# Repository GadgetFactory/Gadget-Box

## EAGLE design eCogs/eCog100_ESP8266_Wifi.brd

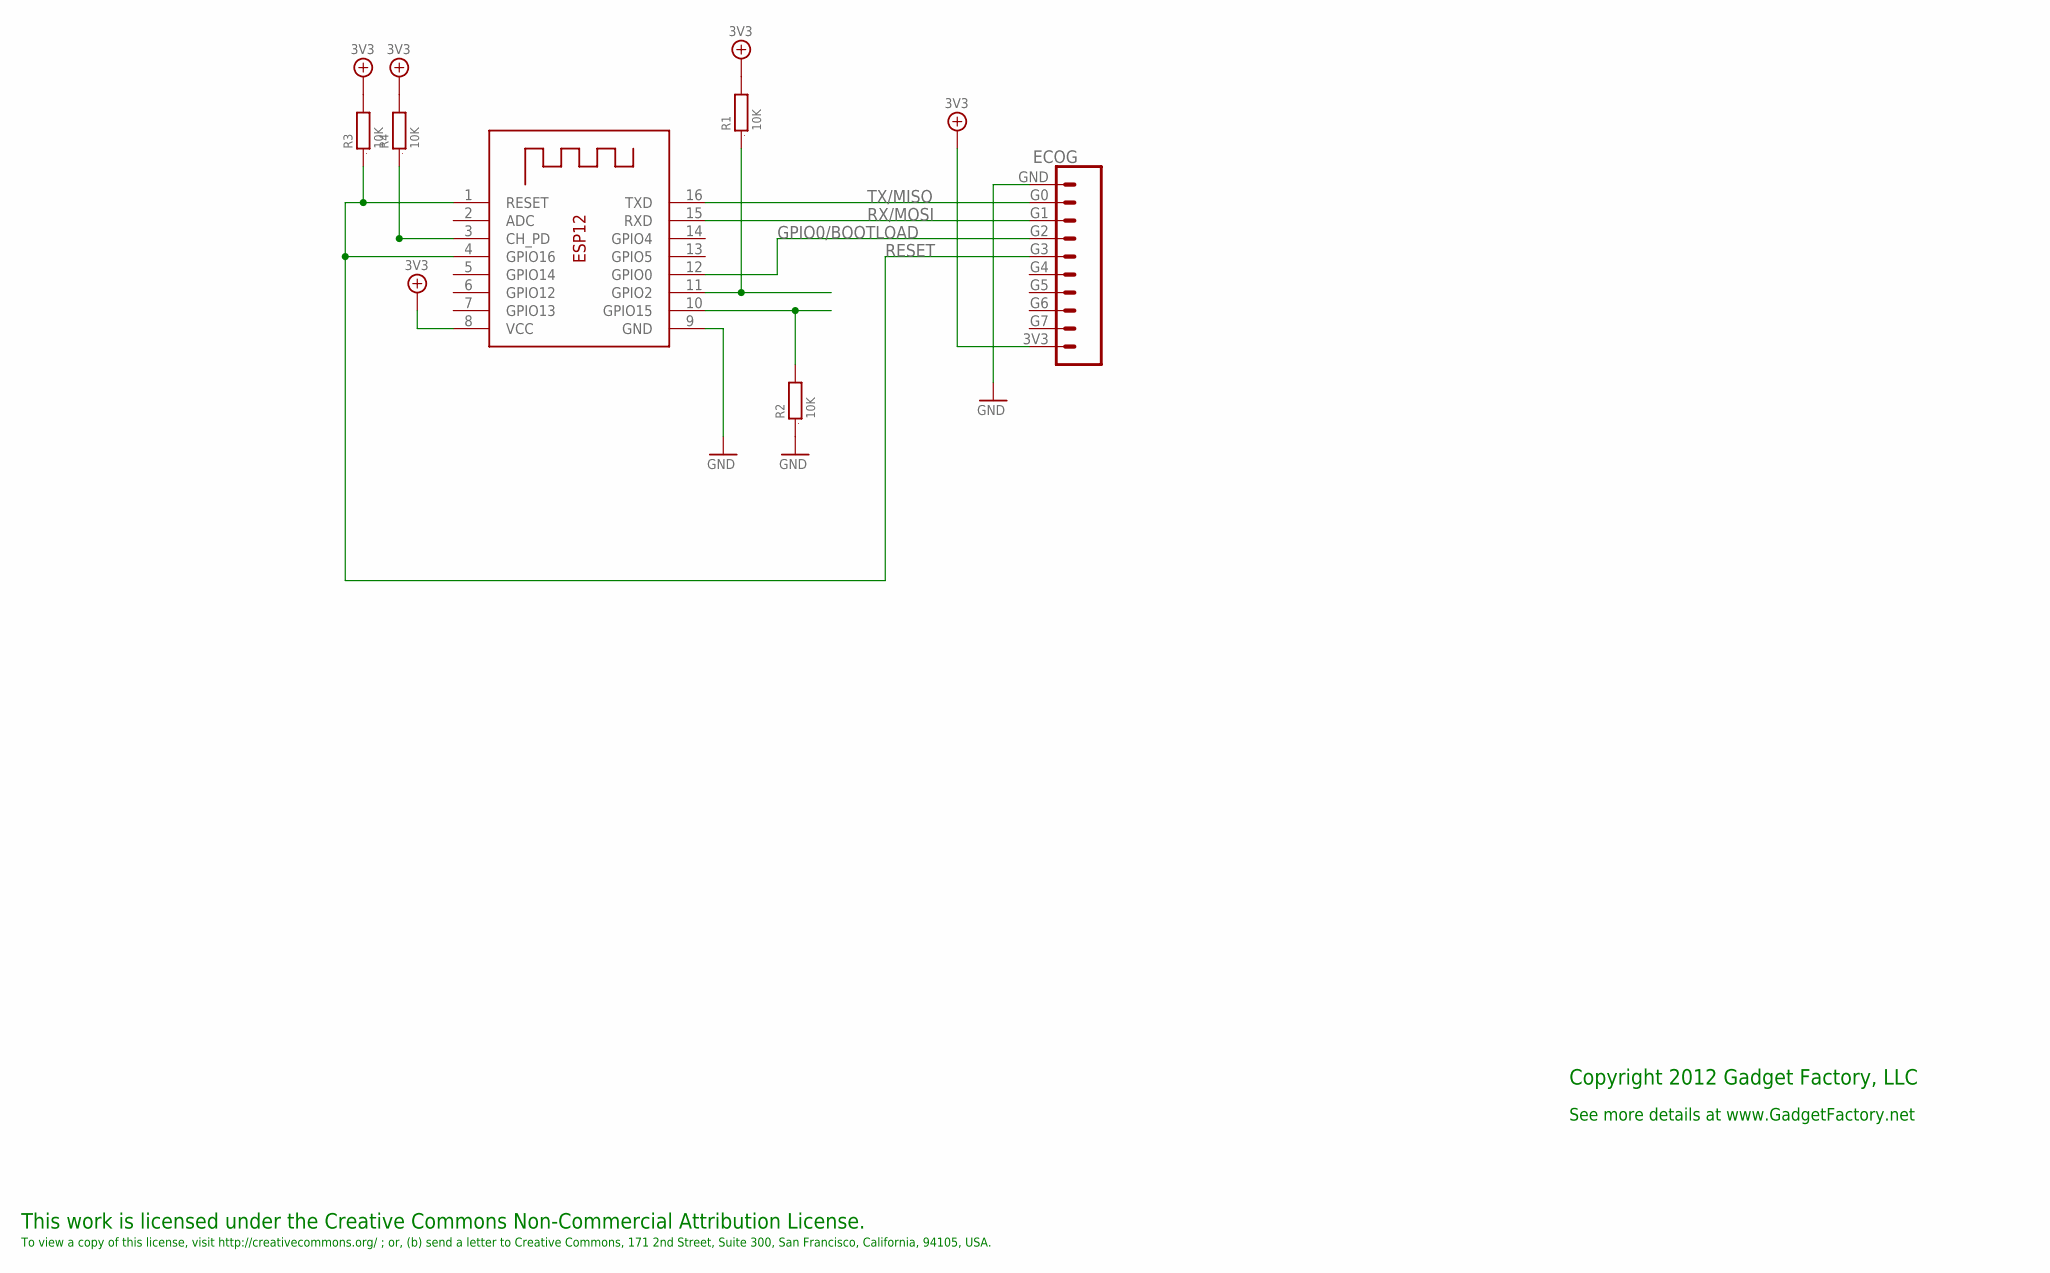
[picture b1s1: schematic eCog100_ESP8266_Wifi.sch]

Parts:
ECOG: ECOG_GENERAL_ROWSURFACEMOUNT; ECOG_GENERAL_SMD
R1, R2, R3, R4: 10K; 0805; DIGIKEY RMCF0805JT10K0CT-ND
X1: ESP-12

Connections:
3V3: ECOG.3V3, R1.2, R3.2, R4.2, X1.8 (VCC)
GND: ECOG.GND, R2.1, X1.9 (GND)
GPIO0/BOOTLOAD: ECOG.G2, X1.12 (GPIO0)
unnamed: R1.1, X1.11 (GPIO2)
unnamed: R2.2, X1.10 (GPIO15)
unnamed: R4.1, X1.3 (CH_PD)
RESET: ECOG.G3, R3.1, X1.1 (RESET), X1.4 (GPIO16)
RX/MOSI: ECOG.G1, X1.15 (RXD)
TX/MISO: ECOG.G0, X1.16 (TXD)

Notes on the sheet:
This work is licensed under the Creative Commons Non-Commercial Attribution License.
To view a copy of this license, visit http://creativecommons.org/ ; or, (b) send a letter to Creative Commons, 171 2nd Street, Suite 300, San Francisco, California, 94105, USA.
Copyright 2012 Gadget Factory, LLC
See more details at www.GadgetFactory.net

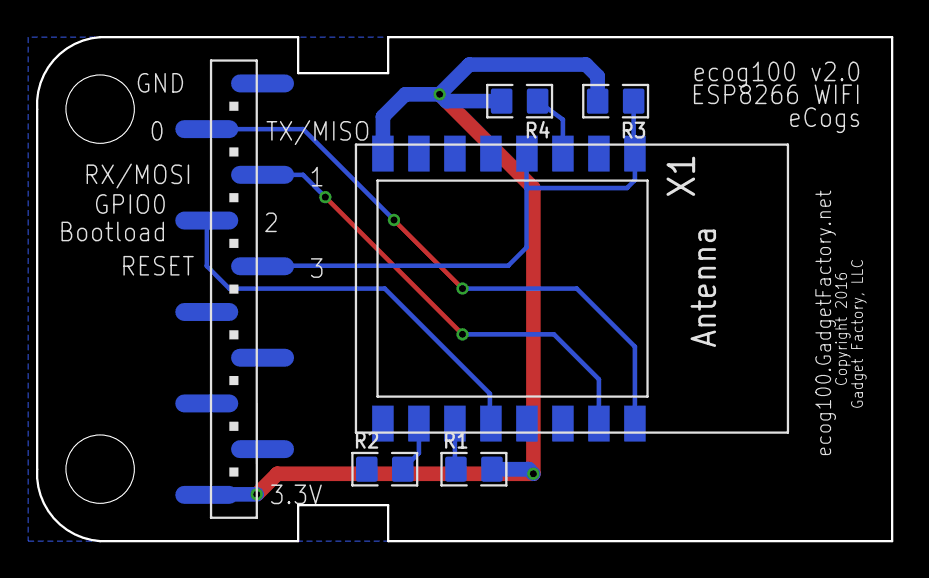
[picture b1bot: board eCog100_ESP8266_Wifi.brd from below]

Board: 2 copper layers, 47.5 x 28.0 mm, 12 parts (5 on the bottom side), 9 nets.

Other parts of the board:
U$1: GADGETBOX_TEXT
U$2, U$3, U$4, U$5: LEGEND_DIO
U$6: OSHW_FILLX200_NOTEXT

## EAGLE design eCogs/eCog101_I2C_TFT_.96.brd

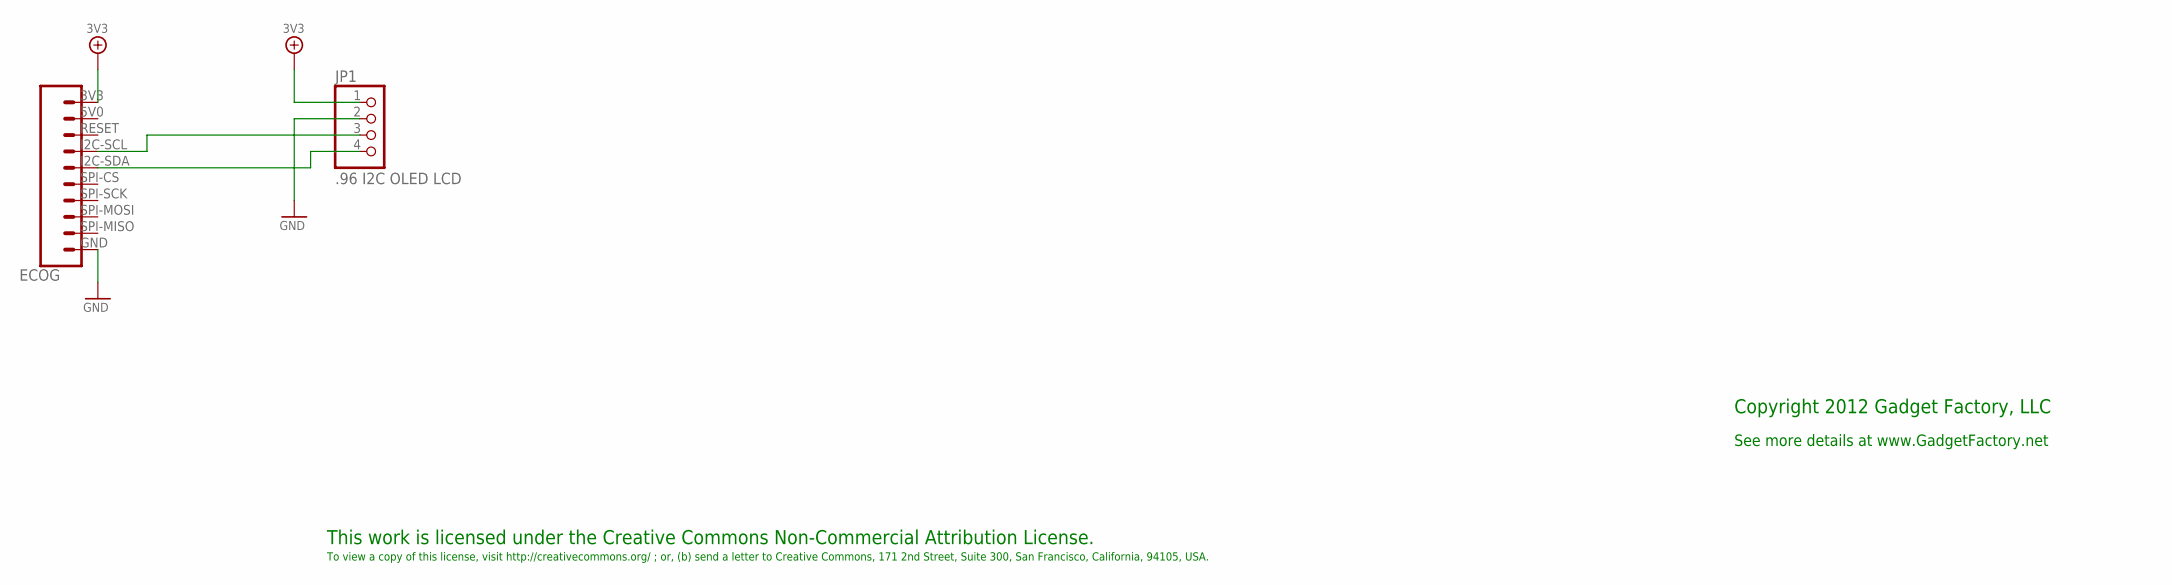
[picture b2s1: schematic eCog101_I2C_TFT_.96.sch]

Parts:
ECOG: ECOG_BUSES_ROWSURFACEMOUNT; ECOG_BUSES_SMD
JP1: .96 I2C OLED LCD; 1X04

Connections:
3V3: ECOG.3V3, JP1.1
GND: ECOG.GND, JP1.2
unnamed: ECOG.I2C-SCL, JP1.3
unnamed: ECOG.I2C-SDA, JP1.4

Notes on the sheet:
This work is licensed under the Creative Commons Non-Commercial Attribution License.
To view a copy of this license, visit http://creativecommons.org/ ; or, (b) send a letter to Creative Commons, 171 2nd Street, Suite 300, San Francisco, California, 94105, USA.
Copyright 2012 Gadget Factory, LLC
See more details at www.GadgetFactory.net

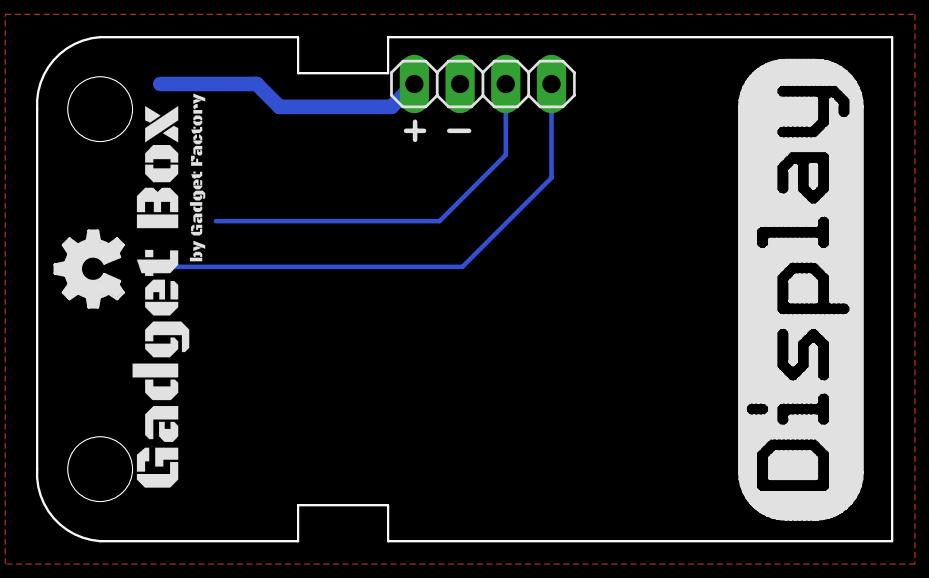
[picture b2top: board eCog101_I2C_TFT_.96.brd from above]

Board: 2 copper layers, 47.5 x 28.0 mm, 4 parts (0 on the bottom side), 4 nets.

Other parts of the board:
U$1: GADGETBOX_SMALL
U$2: OSHW_FILLX150_NOTEXT

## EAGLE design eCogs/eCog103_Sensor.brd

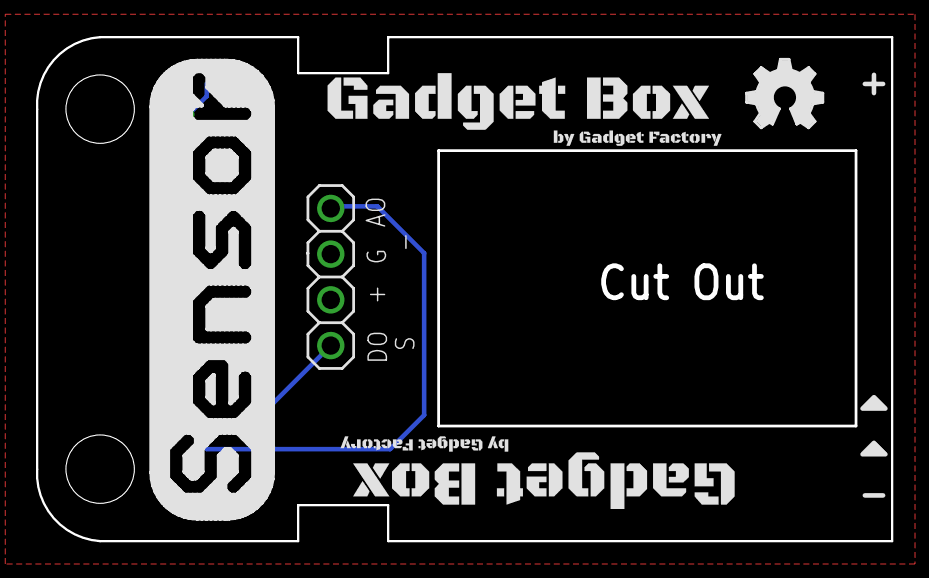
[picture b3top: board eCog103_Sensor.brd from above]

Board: 2 copper layers, 47.5 x 28.0 mm, 7 parts (0 on the bottom side), 4 nets.

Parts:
ECOG: ECOG_GENERAL_ROWSURFACEMOUNT; ECOG_GENERAL_SMD
U$1: SENSOR; SENSOR-HJX4
U$2, U$3: LEGEND_ANALOG
U$4, U$6: GADGETBOX_SMALL
U$5: OSHW_FILLX150_NOTEXT

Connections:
3V3: ECOG.3V3, U$1.+
A1: ECOG.G0, U$1.AO
A2: ECOG.G1, U$1.DO/S
GND: ECOG.GND, U$1.GND

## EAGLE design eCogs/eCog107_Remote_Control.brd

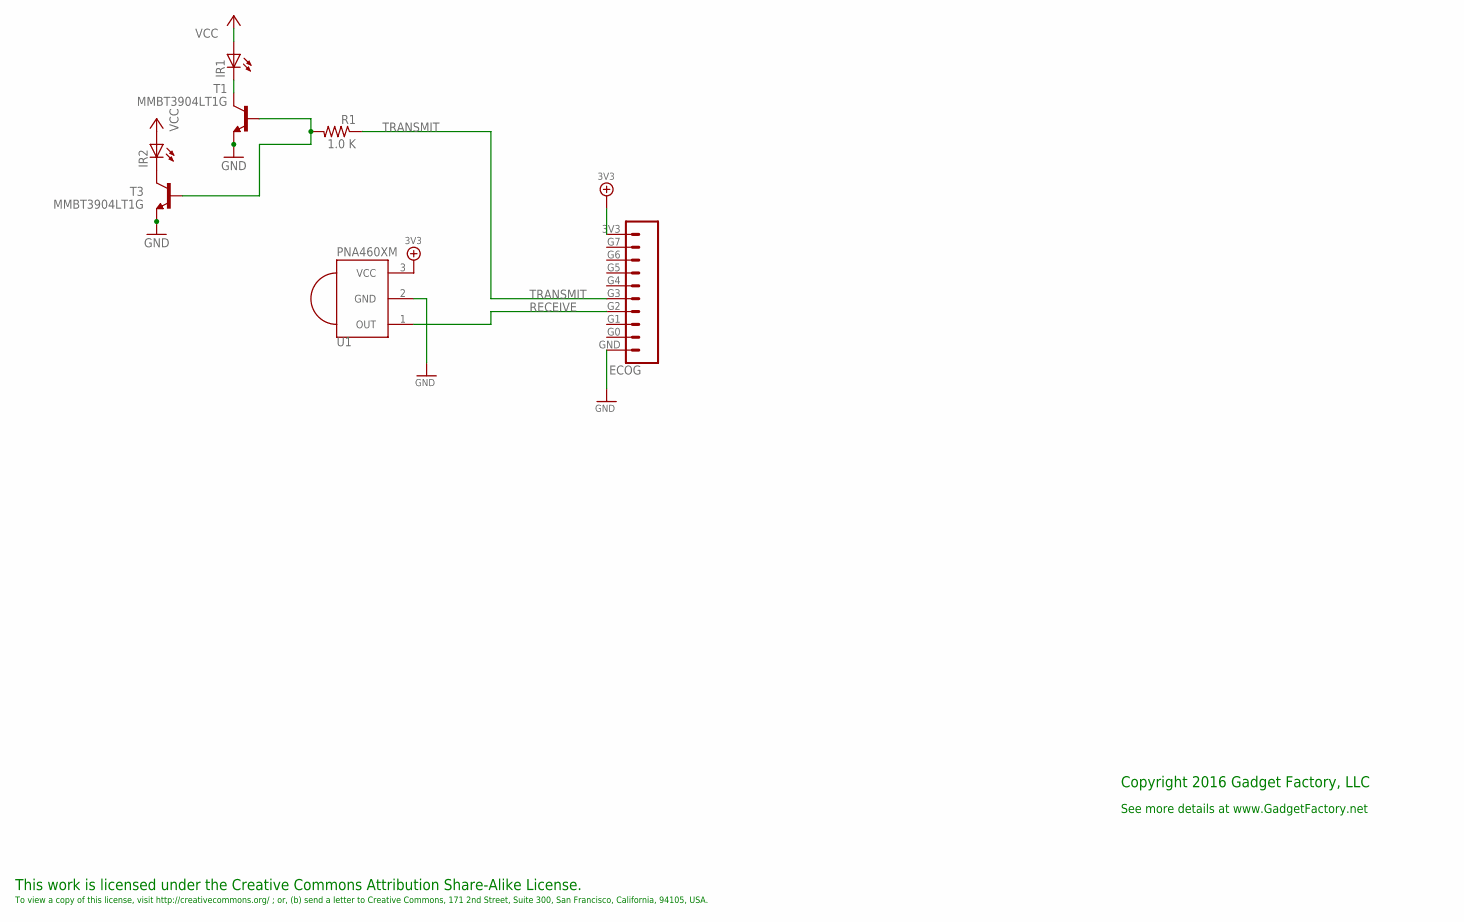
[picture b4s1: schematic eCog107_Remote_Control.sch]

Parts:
ECOG: ECOG_GENERAL_ROWECOG_GENERAL_SMD; ECOG_GENERAL_SMD
IR1: LED5MM; DIGIKEY 1080-1082-ND
IR2: LED5MM; DIGIKEY 1080-1080-ND
R1: 1.0 K; R0805; DIGIKEY 311-1.0KARCT-ND
T1, T3: MMBT3904LT1G; SOT23-BEC; DIGIKEY MMBT3904LT1GOSCT-ND
U1: PNA460XM; DIGIKEY 751-1227-ND

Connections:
3V3: ECOG.3V3, IR1.A, IR2.A, U1.3 (VCC)
GND: ECOG.GND, T1.E, T3.E, U1.2 (GND)
unnamed: IR1.K (C), T1.C
unnamed: IR2.K (C), T3.C
unnamed: R1.2, T1.B, T3.B
RECEIVE: ECOG.G2, U1.1 (OUT)
TRANSMIT: ECOG.G3, R1.1

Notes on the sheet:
This work is licensed under the Creative Commons Attribution Share-Alike License.
To view a copy of this license, visit http://creativecommons.org/ ; or, (b) send a letter to Creative Commons, 171 2nd Street, Suite 300, San Francisco, California, 94105, USA.
Copyright 2016 Gadget Factory, LLC
See more details at www.GadgetFactory.net

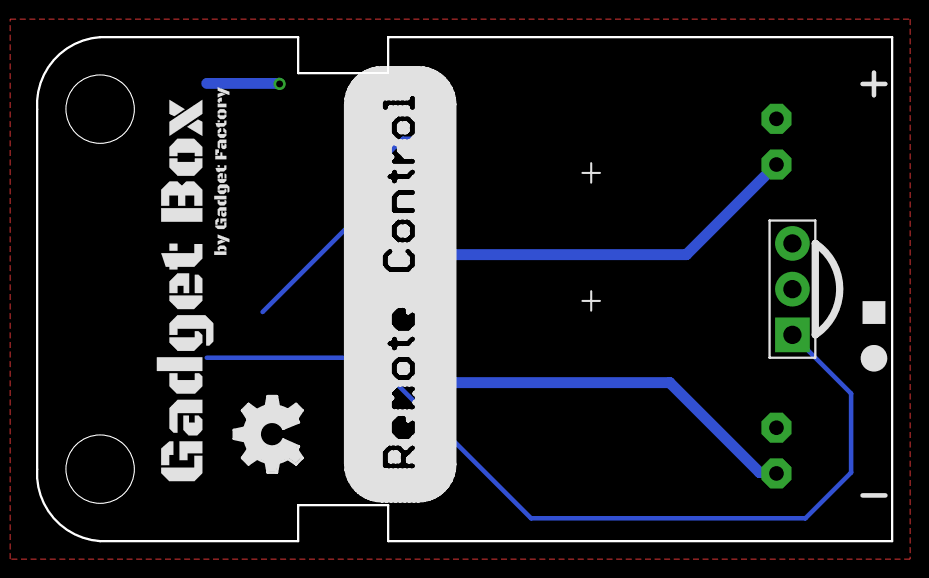
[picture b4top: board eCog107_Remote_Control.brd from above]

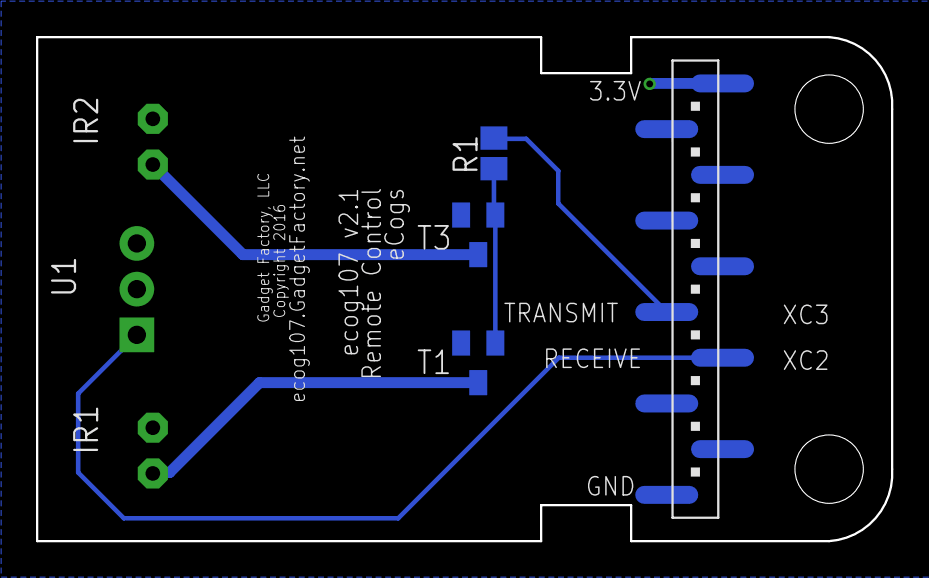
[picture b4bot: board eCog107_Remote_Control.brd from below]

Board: 2 copper layers, 47.5 x 28.0 mm, 11 parts (3 on the bottom side), 7 nets.

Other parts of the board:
U$1: LEGEND_PWM
U$2: LEGEND_DIO
U$5: GADGETBOX_SMALL
U$6: OSHW_FILLX150_NOTEXT

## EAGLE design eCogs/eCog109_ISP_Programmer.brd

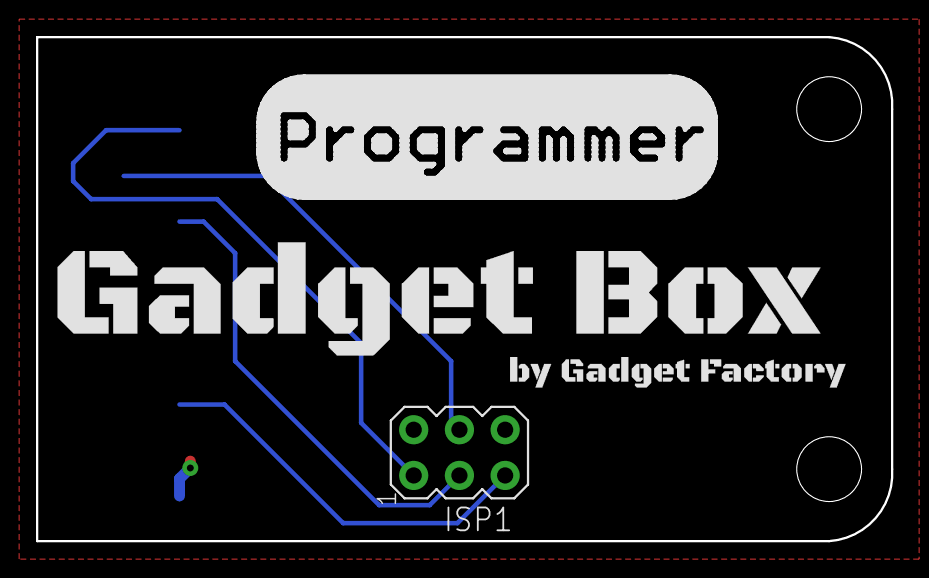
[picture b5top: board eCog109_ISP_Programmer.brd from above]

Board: 2 copper layers, 47.5 x 28.0 mm, 3 parts (0 on the bottom side), 6 nets.

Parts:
ECOG: ECOG_BUSES_ROWECOG_BUSES_SMD; ECOG_BUSES_SMD
ISP1: AVRISP-6; AVRISP
U$1: GADGETBOX_TEXT

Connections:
3V3: ECOG.3V3, ISP1.2
GND: ECOG.GND, ISP1.6
unnamed: ECOG.SPI-MISO, ISP1.1
unnamed: ECOG.SPI-SCK, ISP1.3
unnamed: ECOG.RESET, ISP1.5
unnamed: ECOG.SPI-MOSI, ISP1.4

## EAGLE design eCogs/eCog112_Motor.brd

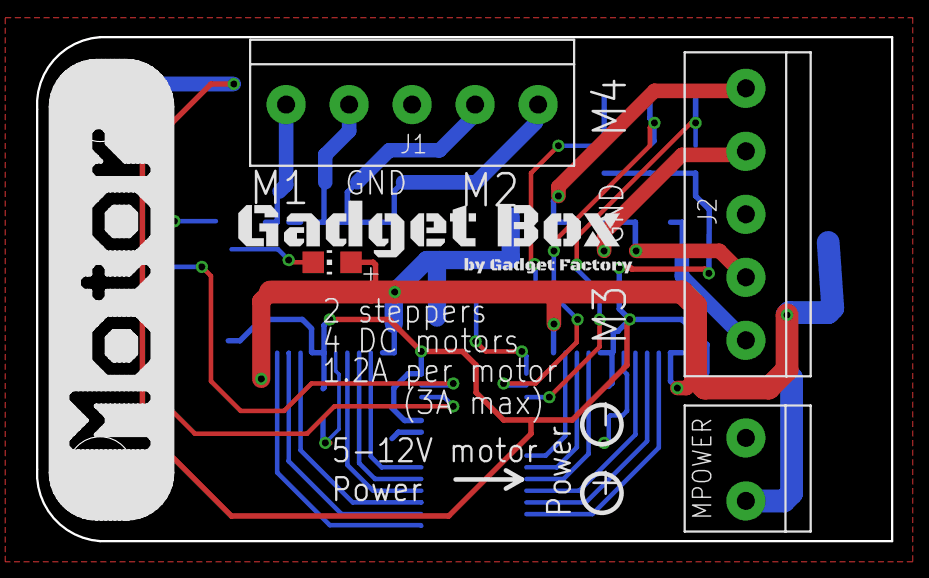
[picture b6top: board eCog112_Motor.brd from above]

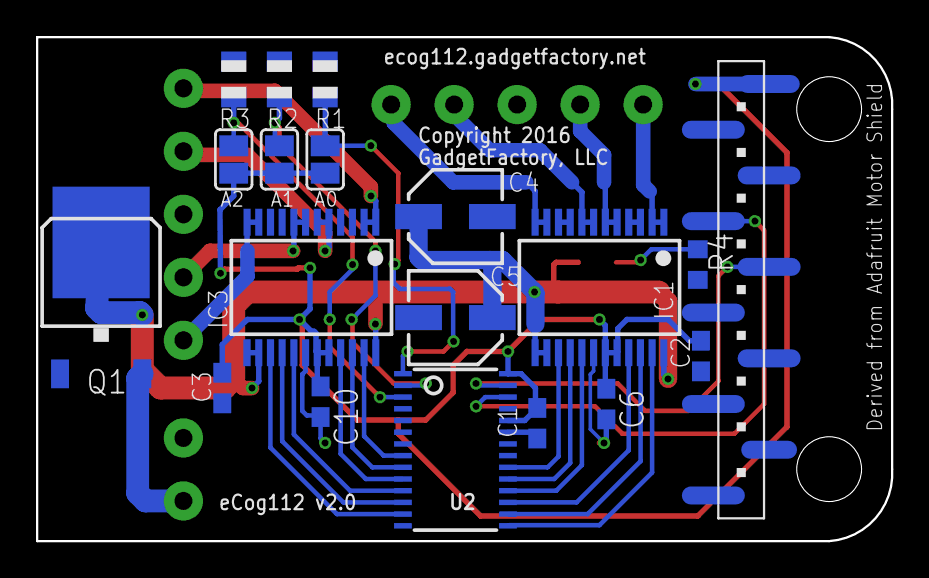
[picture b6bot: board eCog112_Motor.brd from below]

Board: 2 copper layers, 47.5 x 28.0 mm, 24 parts (18 on the bottom side), 30 nets.

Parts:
A0, A1, A2: SJ
C1, C2, C3: 0.1uF; C0603
C4, C5: 47uF/16v; PANASONIC_C
C6, C10: 10uF; C0603
ECOG: ECOG_BUSES_ROWECOG_BUSES_SMD; ECOG_BUSES_SMD
IC1, IC3: TB6612FNG; SSOP24
J1, J2: 1X5; 1X05-3.5MM
LED1: Green; CHIP-LED0805
MPOWER: 1X2-3.5MM
Q1: AOD417; D-PAK_TO252AA
R1, R2, R3: 10k; R0805
R4: 1K; R0603
U2: PCA9685; TSSOP28
U$2: GADGETBOX_SMALL

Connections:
3V3: A0.1, A1.1, A2.1, C1.1, C2.1, C3.1, C6.1, C10.1, ECOG.3V3, IC1.19, IC1.20, IC3.19, IC3.20, U2.24, U2.28
+12V: C4.+, C5.+, IC1.13, IC1.14, IC1.24, IC3.13, IC3.14, IC3.24, LED1.A, Q1.4
A0: A0.2, R1.2, U2.1
A1: A1.2, R2.2, U2.2
A2: A2.2, R3.2, U2.3
GND: C1.2, C2.2, C3.2, C4.-, C5.-, C6.2, C10.2, ECOG.GND, IC1.3, IC1.4, IC1.9, IC1.10, IC1.18, IC3.3, IC3.4, IC3.9, IC3.10, IC3.18, J1.3, J2.3, MPOWER.1, Q1.1, R1.1, R2.1, R3.1, R4.1, U2.4, U2.5, U2.14, U2.23, U2.25
unnamed: IC1.1, IC1.2, J1.1
unnamed: IC1.5, IC1.6, J1.2
unnamed: IC1.7, IC1.8, J1.4
unnamed: IC1.11, IC1.12, J1.5
unnamed: IC3.1, IC3.2, J2.1
unnamed: IC3.5, IC3.6, J2.2
unnamed: IC3.7, IC3.8, J2.4
unnamed: IC3.11, IC3.12, J2.5
unnamed: LED1.C, R4.2
unnamed: MPOWER.2, Q1.3
PWM2: IC3.23, U2.8
PWM3: IC3.22, U2.9
PWM4: IC3.21, U2.10
PWM5: IC3.17, U2.11
PWM6: IC3.16, U2.12
PWM7: IC3.15, U2.13
PWM8: IC1.23, U2.15
PWM9: IC1.22, U2.16
PWM10: IC1.21, U2.17
PWM11: IC1.17, U2.18
PWM12: IC1.16, U2.19
PWM13: IC1.15, U2.20
SCL: ECOG.I2C-SCL, U2.26
SDA: ECOG.I2C-SDA, U2.27

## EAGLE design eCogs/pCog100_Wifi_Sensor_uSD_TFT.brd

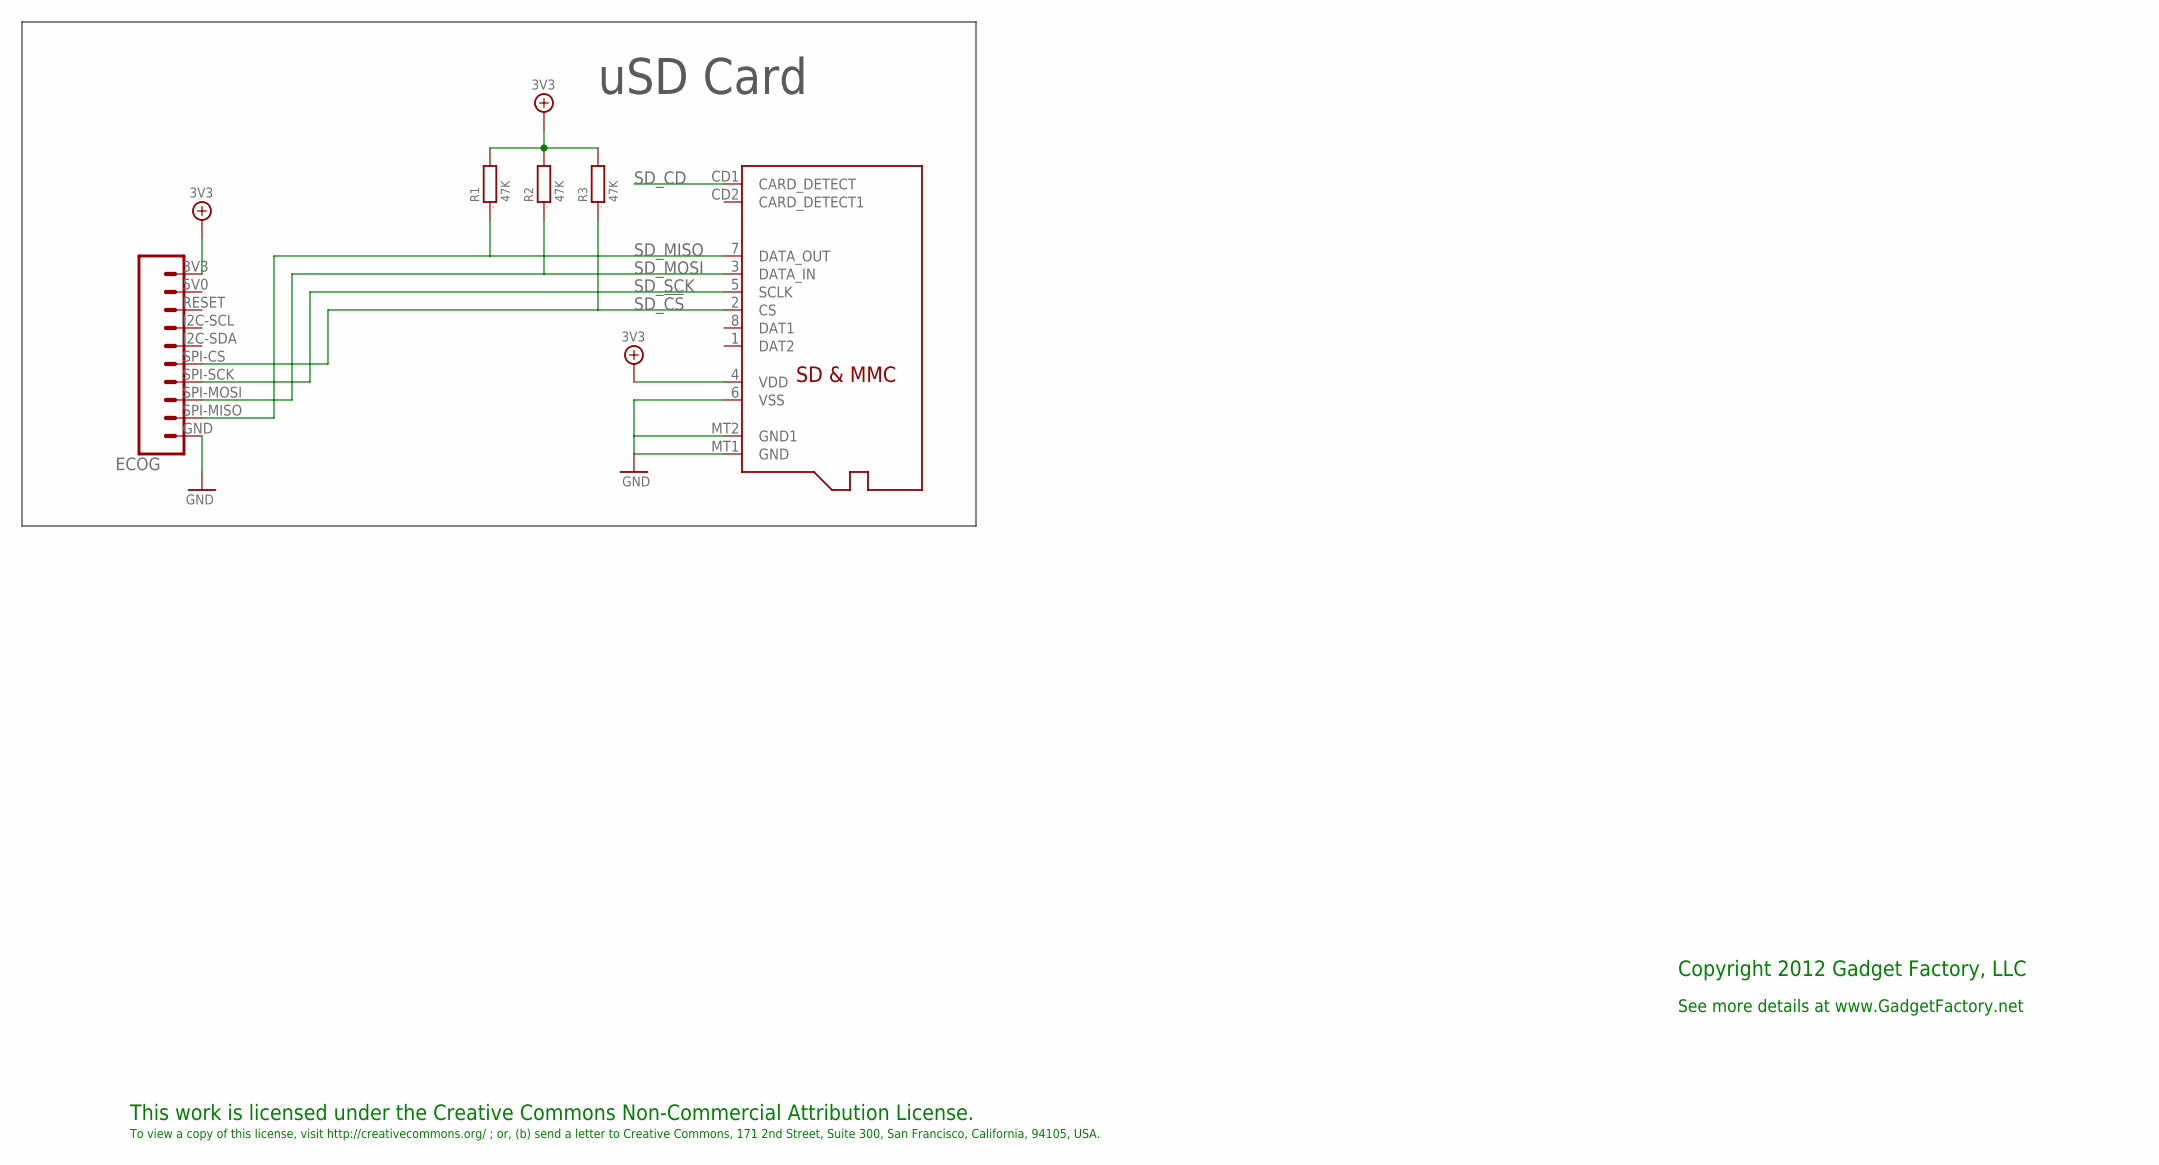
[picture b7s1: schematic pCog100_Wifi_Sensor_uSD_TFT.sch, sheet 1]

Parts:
ECOG: ECOG_BUSES_ROWECOG_BUSES_SMD; ECOG_BUSES_SMD; PARTNO NREC010SABC-M30RC,SULLINS CONNECTOR SOL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
R1, R2, R3: 47K; 0805; PARTNO RMCF0805JT47K0,Stackpole Electronics In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; DIGIKEY RMCF0805JT47K0CT-ND
SD1: MICROSD; PARTNO 101-00660-68-6,Amphenol,dk,101-00660-68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; DIGIKEY 101-00660-68-6-1-ND

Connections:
3V3: ECOG.3V3, R1.2, R2.2, R3.2, SD1.4 (VDD); also elsewhere on the board
GND: ECOG.GND, SD1.6 (VSS), SD1.MT1 (GND), SD1.MT2 (GND1); also elsewhere on the board
SD_!CS: ECOG.SPI-CS, R3.1, SD1.2 (CS)
SD_CD: SD1.CD1 (CARD_DETECT)
SD_MISO: ECOG.SPI-MISO, R1.1, SD1.7 (DATA_OUT)
SD_MOSI: ECOG.SPI-MOSI, R2.1, SD1.3 (DATA_IN)
SD_SCK: ECOG.SPI-SCK, SD1.5 (SCLK)

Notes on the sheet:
This work is licensed under the Creative Commons Non-Commercial Attribution License.
To view a copy of this license, visit http://creativecommons.org/ ; or, (b) send a letter to Creative Commons, 171 2nd Street, Suite 300, San Francisco, California, 94105, USA.
Copyright 2012 Gadget Factory, LLC
See more details at www.GadgetFactory.net
uSD Card

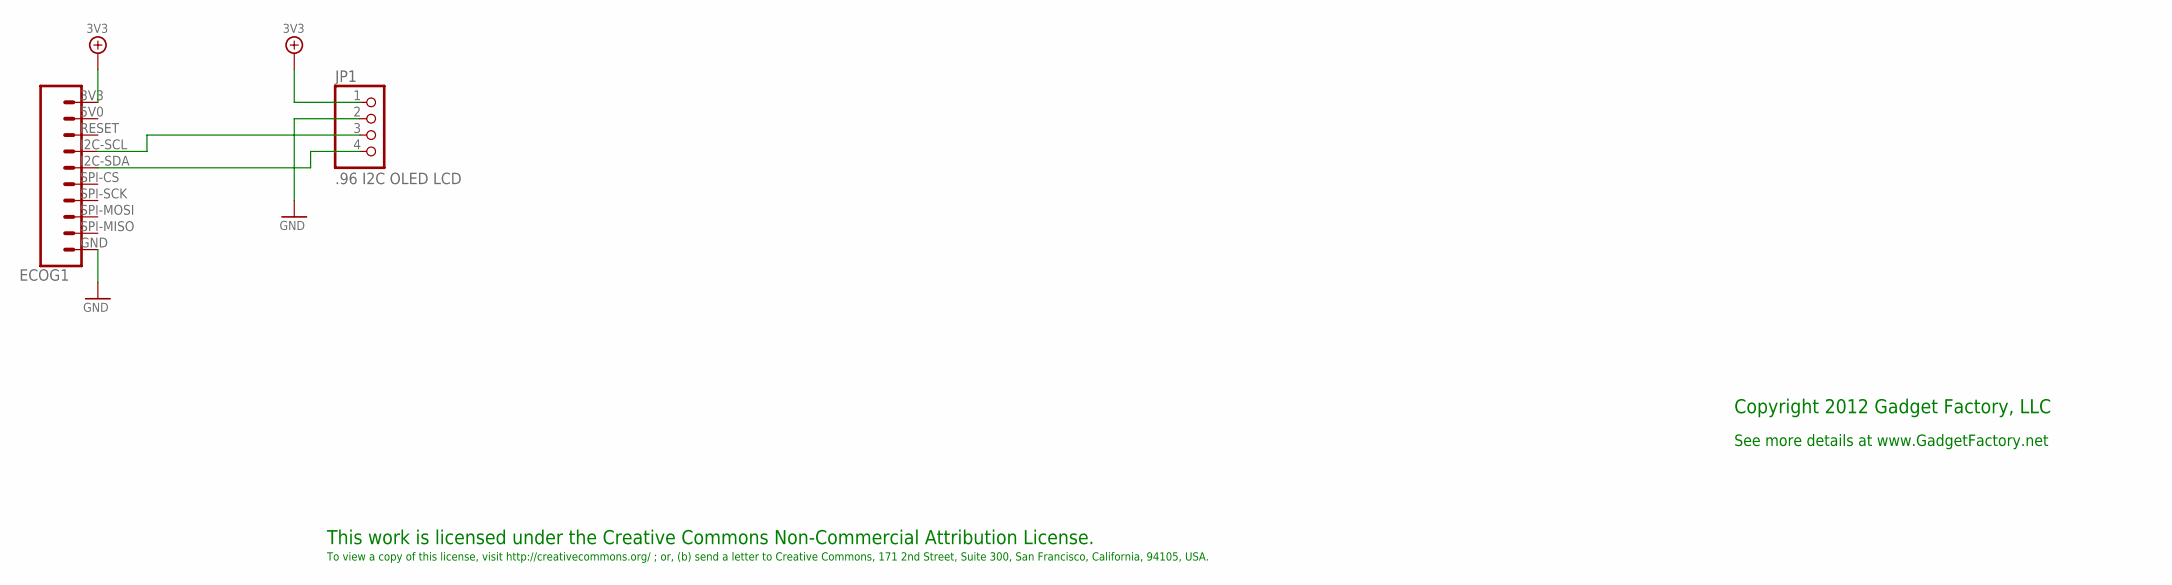
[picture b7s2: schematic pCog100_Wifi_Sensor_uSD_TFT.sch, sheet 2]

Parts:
ECOG1: ECOG_BUSES_ROWECOG_BUSES_SMD; ECOG_BUSES_SMD; PARTNO NREC010SABC-M30RC,SULLINS CONNECTOR SOL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
JP1: .96 I2C OLED LCD; 1X04; PARTNO 346540,unknown,seeed,346540,"0.96"" 128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

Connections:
3V3: ECOG1.3V3, JP1.1; also elsewhere on the board
GND: ECOG1.GND, JP1.2; also elsewhere on the board
unnamed: ECOG1.I2C-SCL, JP1.3
unnamed: ECOG1.I2C-SDA, JP1.4

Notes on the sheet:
This work is licensed under the Creative Commons Non-Commercial Attribution License.
To view a copy of this license, visit http://creativecommons.org/ ; or, (b) send a letter to Creative Commons, 171 2nd Street, Suite 300, San Francisco, California, 94105, USA.
Copyright 2012 Gadget Factory, LLC
See more details at www.GadgetFactory.net

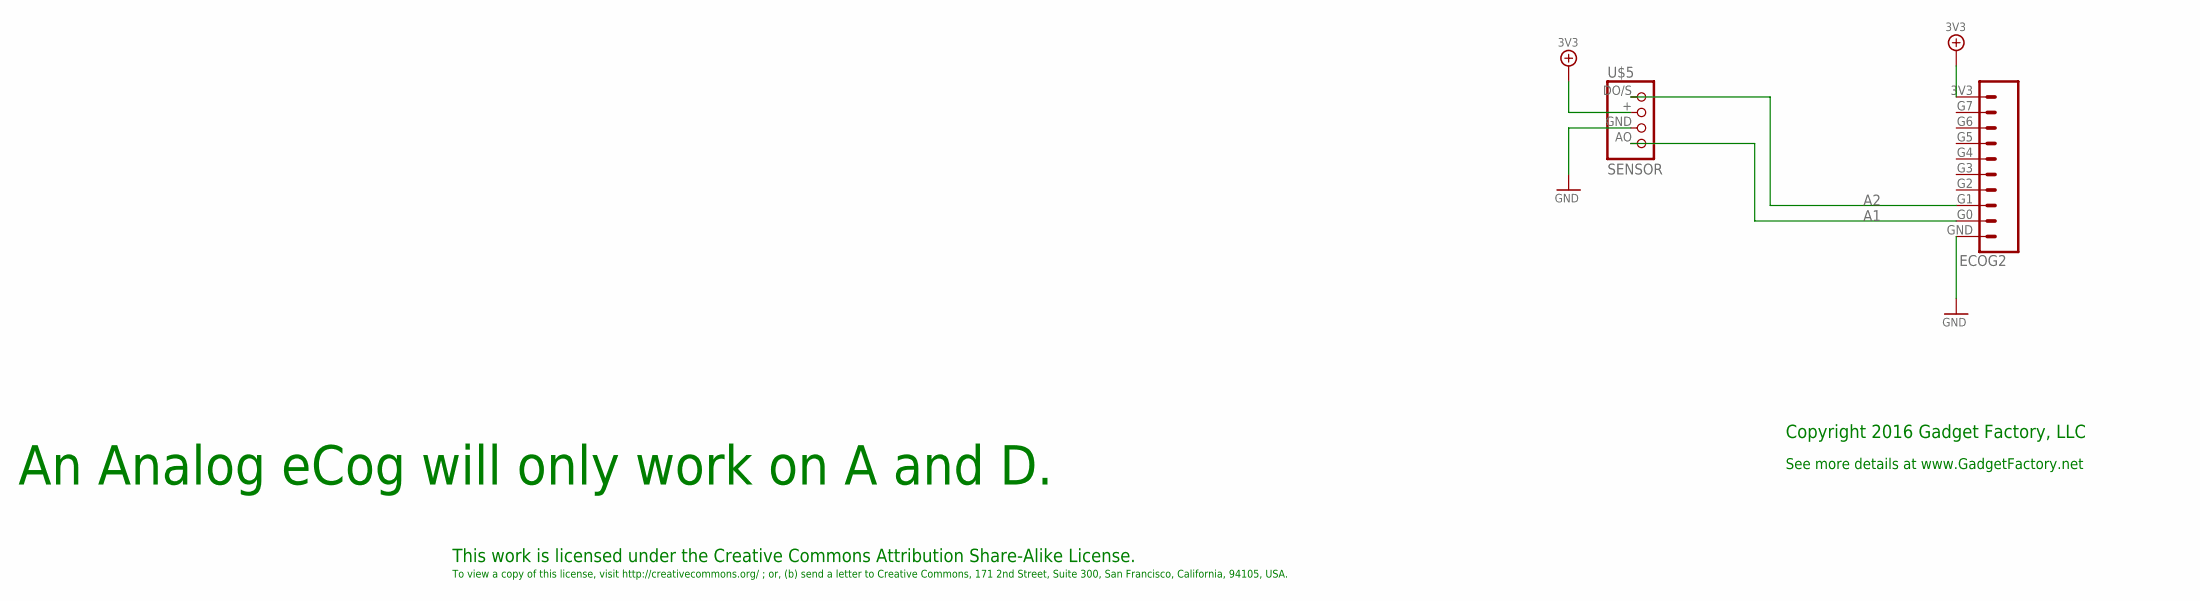
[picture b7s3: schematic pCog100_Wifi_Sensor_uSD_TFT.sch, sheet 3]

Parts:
ECOG2: ECOG_GENERAL_ROWECOG_GENERAL_SMD; ECOG_GENERAL_SMD; PARTNO NREC010SABC-M30RC,SULLINS CONNECTOR SOL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
U$5: SENSOR; SENSOR-HJX4

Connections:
3V3: ECOG2.3V3, U$5.+; also elsewhere on the board
A1: ECOG2.G0, U$5.AO
A2: ECOG2.G1, U$5.DO/S
GND: ECOG2.GND, U$5.GND; also elsewhere on the board

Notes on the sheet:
This work is licensed under the Creative Commons Attribution Share-Alike License.
To view a copy of this license, visit http://creativecommons.org/ ; or, (b) send a letter to Creative Commons, 171 2nd Street, Suite 300, San Francisco, California, 94105, USA.
Copyright 2016 Gadget Factory, LLC
See more details at www.GadgetFactory.net
An Analog eCog will only work on A and D.

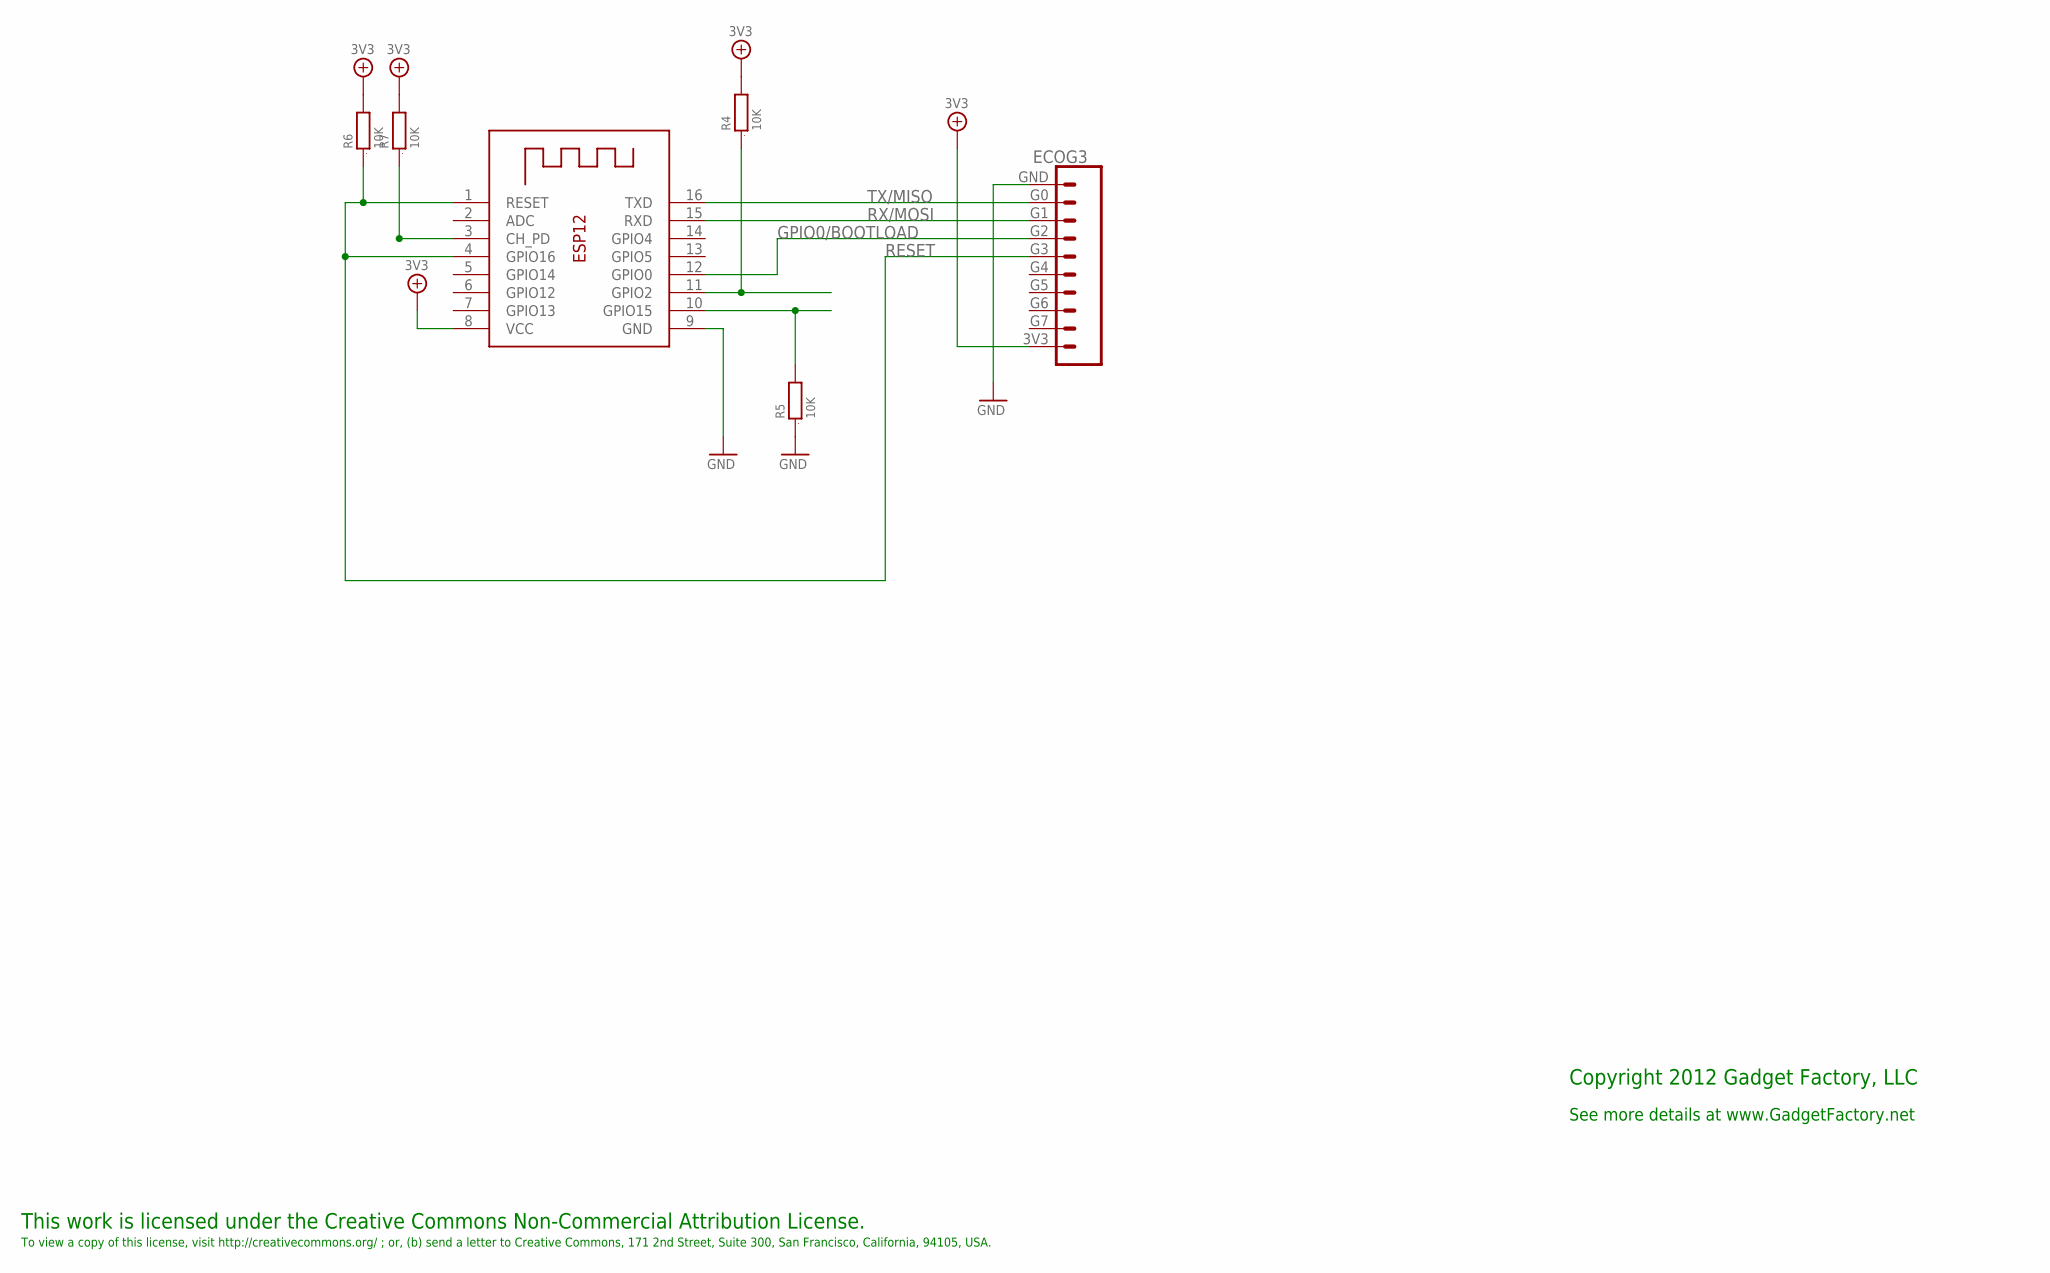
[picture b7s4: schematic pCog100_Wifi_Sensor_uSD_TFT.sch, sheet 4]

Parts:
ECOG3: ECOG_GENERAL_ROWECOG_GENERAL_SMD; ECOG_GENERAL_SMD; PARTNO NREC010SABC-M30RC,SULLINS CONNECTOR SOL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
R4, R5, R6, R7: 10K; 0805; PARTNO RC0805JR-0710KL,YAGEO (VA),dk,311-10KAR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; DIGIKEY RMCF0805JT10K0CT-ND
X1: ESP-12; PARTNO 385646,AI-Thinker,dx.com,385646,ESP8266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

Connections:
3V3: ECOG3.3V3, R4.2, R6.2, R7.2, X1.8 (VCC); also elsewhere on the board
GND: ECOG3.GND, R5.1, X1.9 (GND); also elsewhere on the board
GPIO0/BOOTLOAD: ECOG3.G2, X1.12 (GPIO0)
unnamed: R4.1, X1.11 (GPIO2)
unnamed: R5.2, X1.10 (GPIO15)
unnamed: R7.1, X1.3 (CH_PD)
RESET: ECOG3.G3, R6.1, X1.1 (RESET), X1.4 (GPIO16)
RX/MOSI: ECOG3.G1, X1.15 (RXD)
TX/MISO: ECOG3.G0, X1.16 (TXD)

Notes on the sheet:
This work is licensed under the Creative Commons Non-Commercial Attribution License.
To view a copy of this license, visit http://creativecommons.org/ ; or, (b) send a letter to Creative Commons, 171 2nd Street, Suite 300, San Francisco, California, 94105, USA.
Copyright 2012 Gadget Factory, LLC
See more details at www.GadgetFactory.net

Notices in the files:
parts and their libraries:
microbuilder: This work is placed in the public domain, and may be freely used for commercial and non-commercial work with the following conditions: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
SparkFun: Licensing: CC v3.0 Share-Alike You are welcome to use this library for commercial purposes.
